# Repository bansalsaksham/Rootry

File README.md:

# Rootry (formerly SoilHawk) | Automatic Irrigation System

An evolving hardware IoT project focused on providing low-cost, high-efficiency, solar-powered precision irrigation for smallholder farms in India. What began as an award-winning science exhibition prototype has evolved into a field-tested product architecture achieving significant water conservation.

**Key Achievements:**
* 🏆 **Runner-up (2nd Worldwide):** UPenn EcoVenture Global Climate Venture Competition (2024)

* 🏆 **Winner:** CBSE National Science Exhibition (2019) & Regional Science Exhibition (2018-19)
* 🌟 **Government Recognition:** Recommended as *Jal Doot* by the Ministry of Jal Shakti

---

## 🚀 The Product Evolution

This project has undergone several architectural iterations, moving from a basic microcontroller logic proof-of-concept to a distributed ML concept, and finally to a robust, custom ESP32 IoT system.

### Phase 3: Rootry v2 (Current Architecture - 2024 to Present)
The current iteration focuses on productization, robustness, and real-world deployment constraints. Designed for areas with limited grid power and no smartphone access, keeping the unit cost under ₹4,000.

* **Verified Impact:** Field-tested across a 4-acre site, achieving a **30% reduction** in water usage (250 L/m² vs control of 360 L/m²).
* **Hardware Stack:** * Custom PCB designed in **KiCad**.
  * **MCU:** ESP32-S3 (Dual-core 240MHz) replacing the legacy Arduino architecture.
  * **Connectivity:** Hybrid Dual GSM (SIM800L via UART AT commands) + WiFi interface.
  * **Power:** 10W Solar Panel + 12V SLA Battery with PWM charge controller.
* **Firmware Improvements:**
  * Replaced all legacy `delay()` calls with non-blocking loops using `millis()`.
  * Implemented **Hysteresis Band Control**: Pump turns ON below 30% moisture and OFF above 50% to prevent rapid toggling.
  * **Adaptive Temperature Compensation:** Stop thresholds dynamically raise to 60% when ambient temperatures exceed 35°C (read via DHT22).
  * **Web Dashboard:** `ESPAsyncWebServer` integration for a real-time localized dashboard.

---

### Phase 2: SoilHawk (2023 - ImpactHack Sponsor Track Winner)
A conceptual expansion into a distributed, multi-node architecture utilizing both ground-based sensing and aerial diagnostic telemetry. This phase validated the integration of machine learning for targeted agricultural interventions.

---

### Phase 1: The Foundation (2019 Prototype)
The genesis of the project. A standalone prototype built to demonstrate the core viability of automated soil moisture management to prevent soil degradation and conserve water. 

* **The Setup:** Arduino Uno, FC-28 Soil Moisture Sensor, DHT11 Temperature/Humidity Sensor, 16x2 LCD, 5V Relay for water pump actuation, and a basic GSM module.
* **Logic:** Basic linear logic. The system reads analog moisture thresholds. If the soil falls below `MAXDRYNESS 600`, the pump is triggered, and the GSM module dispatches an SMS alert ("Motor Start") to the farmer.
* **Validation:** Documented in a formal research paper analyzing the mathematical and environmental impact, endorsed by Dr. Sumeet Gill, Professor of Computer Science at MDU Rohtak.

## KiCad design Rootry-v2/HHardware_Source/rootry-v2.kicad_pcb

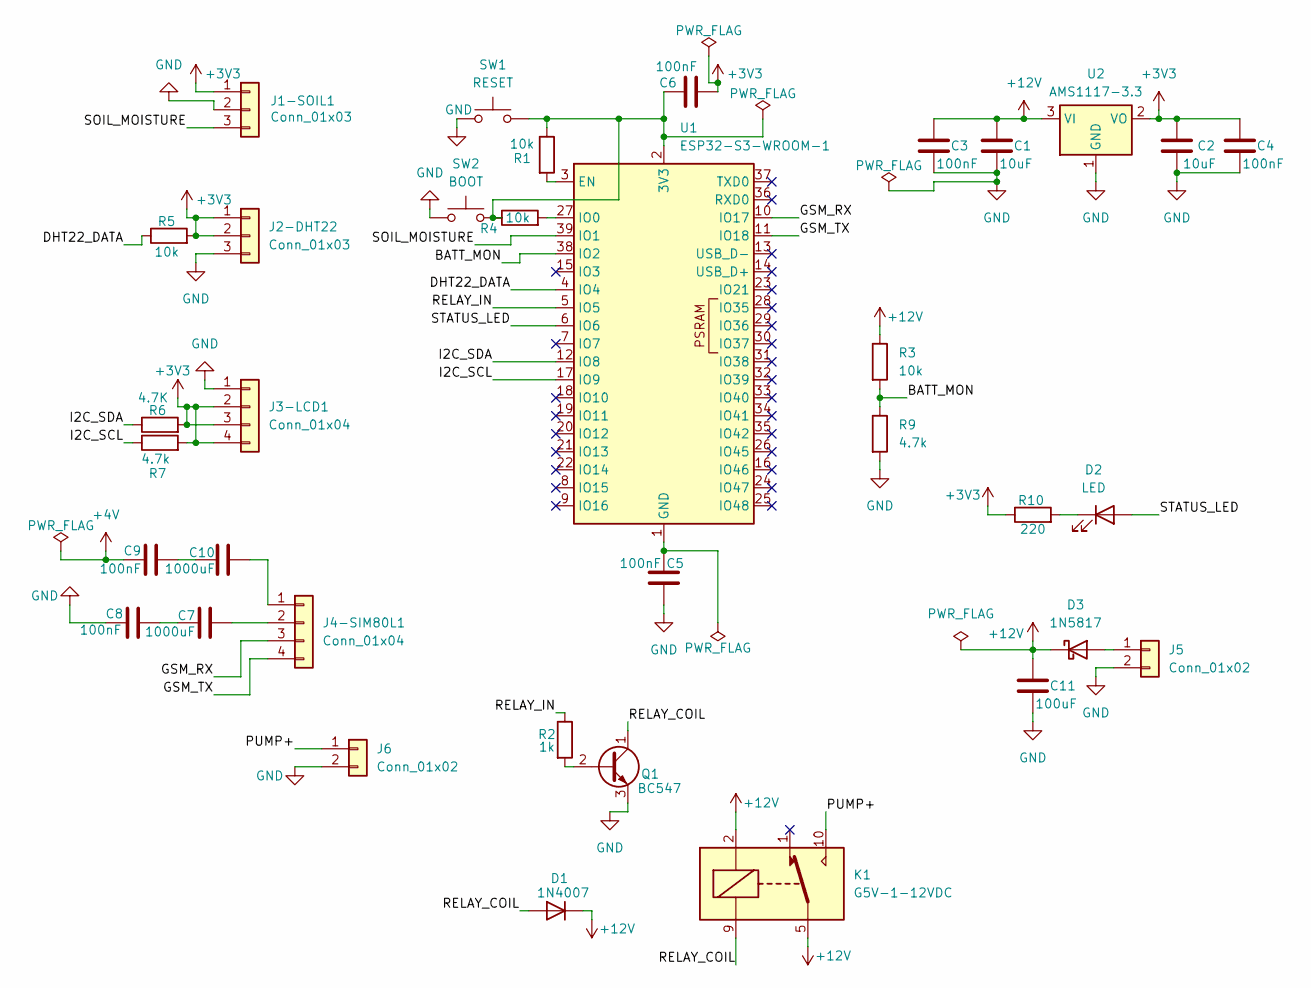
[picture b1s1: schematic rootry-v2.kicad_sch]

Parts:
C1, C2: 10uF; CP_Radial_D5.0mm_P2.50mm
C3, C4, C5, C6, C8, C9: 100nF; C_Disc_D5.0mm_W2.5mm_P5.00mm
C7, C10: 1000uF; CP_Radial_D10.0mm_P5.00mm
C11: 100uF; CP_Radial_D6.3mm_P2.50mm
D1: 1N4007; D_DO-41_SOD81_P10.16mm_Horizontal
D2: LED; LED_D5.0mm
D3: 1N5817; D_DO-41_SOD81_P10.16mm_Horizontal
J1-SOIL1, J2-DHT22: Conn_01x03; PinHeader_1x03_P2.54mm_Vertical
J3-LCD1, J4-SIM80L1: Conn_01x04; PinHeader_1x04_P2.54mm_Vertical
J5, J6: Conn_01x02; TerminalBlock_MaiXu_MX126-5.0-02P_1x02_P5.00mm
K1: G5V-1-12VDC; Relay_SPDT_Omron_G5V-1
Q1: BC547; TO-92_Inline
R1, R3, R4, R5: 10k; R_Axial_DIN0207_L6.3mm_D2.5mm_P10.16mm_Horizontal
R2: 1k; R_Axial_DIN0207_L6.3mm_D2.5mm_P10.16mm_Horizontal
R6: 4.7K; R_Axial_DIN0207_L6.3mm_D2.5mm_P10.16mm_Horizontal
R7, R9: 4.7k; R_Axial_DIN0207_L6.3mm_D2.5mm_P10.16mm_Horizontal
R10: 220; R_Axial_DIN0207_L6.3mm_D2.5mm_P10.16mm_Horizontal
SW1: RESET; SW_PUSH_6mm_H5mm
SW2: BOOT; SW_PUSH_6mm_H5mm
U1: ESP32-S3-WROOM-1
U2: AMS1117-3.3; SOT-223-3_TabPin2

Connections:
+3V3: C2.1, C4.1, C6.1, J1-SOIL1.1, J2-DHT22.1, J2-DHT22.2, J3-LCD1.2, J3-LCD1.3, J3-LCD1.4, R5.2, R6.2, R7.2, R10.1, U2.2 (VO)
+4V: C9.1
+12V: C1.1, C3.1, C11.1, D1.1 (K), D3.1 (K), K1.2, K1.5, K1.6, R3.1, U2.3 (VI)
/BATT_MON: R3.2, R9.1, U1.38 (IO2)
/DHT22_DATA: R5.1, U1.4 (IO4)
/GSM_RX: J4-SIM80L1.3, U1.10 (IO17)
/GSM_TX: J4-SIM80L1.4, U1.11 (IO18)
/I2C_SCL: R7.1, U1.17 (IO9)
/I2C_SDA: R6.1, U1.12 (IO8)
/PUMP+: J6.1, K1.10
/RELAY_COIL: D1.2 (A), K1.9, Q1.1 (C)
/RELAY_IN: R2.1, U1.5 (IO5)
/SOIL_MOISTURE: J1-SOIL1.3, U1.39 (IO1)
/STATUS_LED: D2.2 (A), U1.6 (IO6)
GND: C1.2, C2.2, C3.2, C4.2, C5.1, C8.1, C11.2, J1-SOIL1.2, J2-DHT22.3, J3-LCD1.1, J5.2, J6.2, Q1.3 (E), R9.2, SW1.1, SW2.1, U2.1 (GND)
unnamed: C5.2, U1.1 (GND), U1.40 (GND), U1.41 (GND)
unnamed: C7.1, C8.2
unnamed: C9.2, C10.1
unnamed: D2.1 (K), R10.2
unnamed: D3.2 (A), J5.1
unnamed: C10.2, J4-SIM80L1.1
unnamed: C7.2, J4-SIM80L1.2
unnamed: Q1.2 (B), R2.2
unnamed: C6.2, R1.1, R4.1, SW1.2, SW2.2, U1.2 (3V3)
unnamed: R1.2, U1.3 (EN)
unnamed: R4.2, U1.27 (IO0)

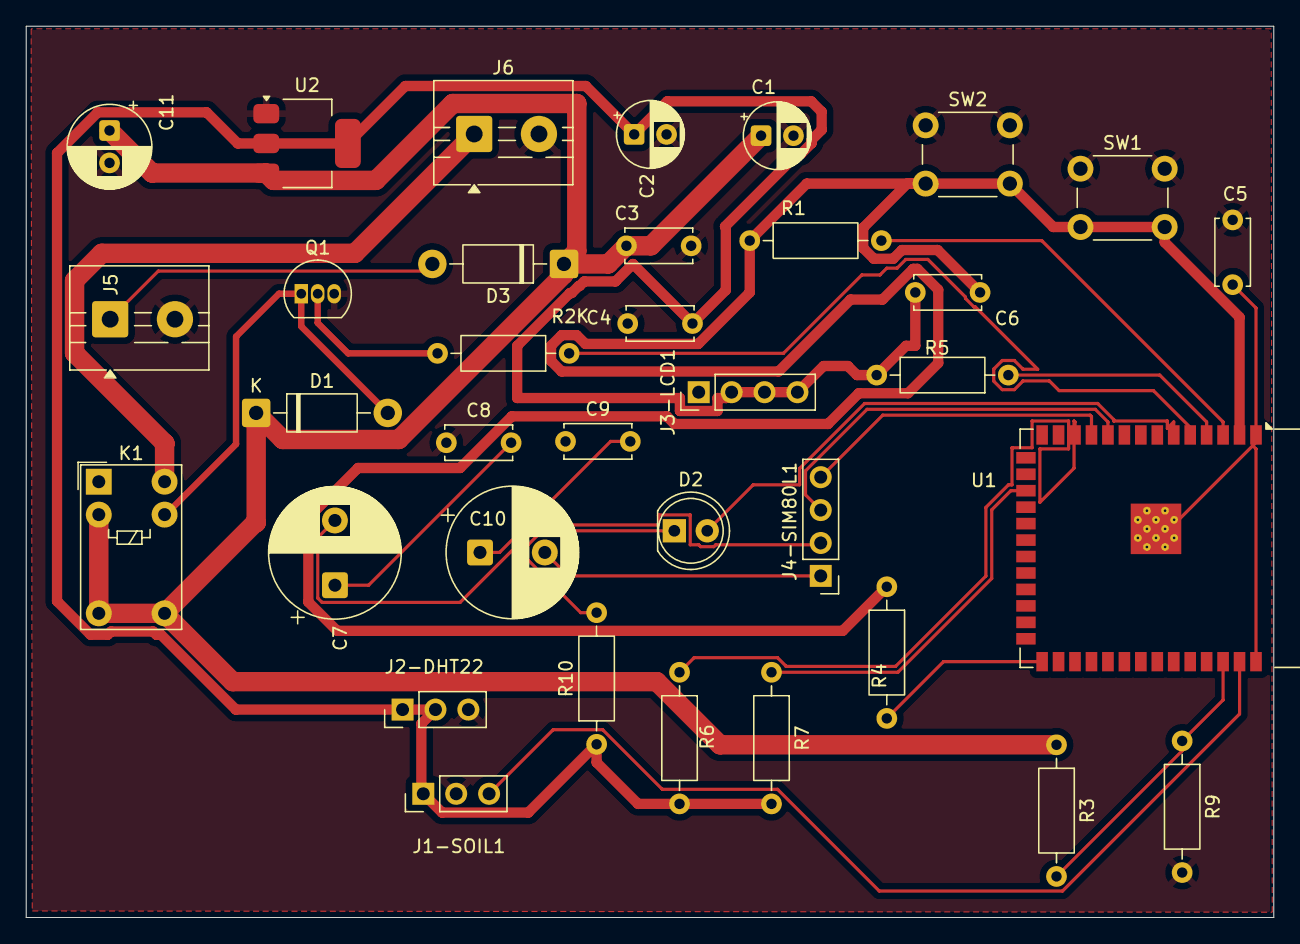
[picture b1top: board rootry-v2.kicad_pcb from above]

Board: 2 copper layers, 96.3 x 68.8 mm, 35 parts (0 on the bottom side), 25 nets.

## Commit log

2026-06-26 Rename rootry-v2-drl.rpt to Rootry-v2/Manufacturing/Gerbers/rootry-v2-drl.rpt
2026-06-26 Rename Rootry-v2/Manufacturing/Gerbers/rootry-v2-B_Cu.gbl to Rootry-v2/rootry-v2-B_Cu.gbl
2026-06-26 Rename Rootry-v2/rootry-v2-B_Cu.gbl to Rootry-v2/Manufacturing/rootry-v2-B_Cu.gbl
2026-06-26 Rename Rootry-v2/Manufacturing/rootry-v2-B_Cu.gbl to Rootry-v2/Manufacturing/Gerbers/rootry-v2-B_Cu.gbl
2026-06-26 Rename Rootry-v2/rootry-v2.kicad_pcb to Rootry-v2/hardware_Source/rootry-v2.kicad_pcb
2026-06-26 Rename rootry-v2.kicad_pcb to rootry-v2.kicad_pcb
2026-06-26 Rename Rootry-v2/rootry-v2.kicad_pro to Rootry-v2/Hardware_Source/rootry-v2.kicad_pro
2026-06-26 Rename Rootry-v2/rootry-v2.kicad_sch to Rootry-v2/Hardware_Source/rootry-v2.kicad_sch
